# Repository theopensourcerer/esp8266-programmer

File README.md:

# esp8266-programmer
WIP - ESP Device Programmer without solder

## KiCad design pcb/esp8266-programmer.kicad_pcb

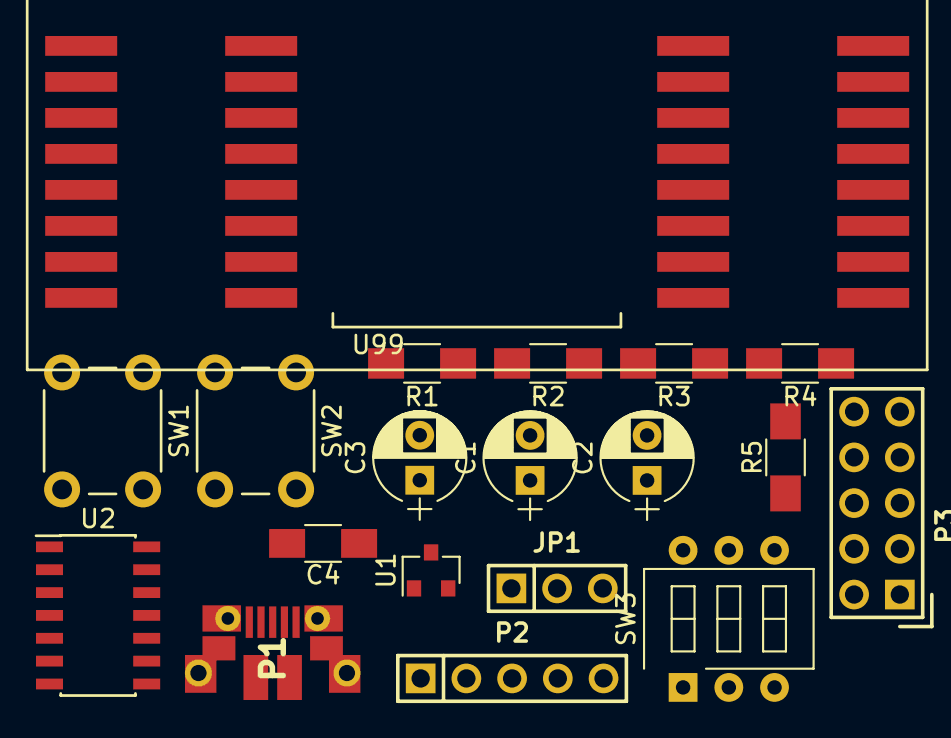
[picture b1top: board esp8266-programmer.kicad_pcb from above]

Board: 2 copper layers, 19 parts (0 on the bottom side), 23 nets, no tracks yet.

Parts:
C1: 1uF; CP_Radial_D5.0mm_P2.50mm
C2: 330uf; CP_Radial_D5.0mm_P2.50mm
C3: 4.7uF; CP_Radial_D5.0mm_P2.50mm
C4: 330nF; C_1206_HandSoldering
JP1: Jumper_NO_Dual; SIL-3
P1: USB_OTG; USB-MICROB-FCI-10103592
P2: CONN_01X04; SIL-5
P3: CONN_02X05; DIL-5
R1, R2, R3, R4, R5: 10K; R_1206_HandSoldering
SW1: RESET; SW_PUSH_6mm_h4.3mm
SW2: FLASH; SW_PUSH_6mm_h4.3mm
SW3: SW_DP3T; SW_DIP_x3_W7.62mm_Slide_LowProfile
U1: MCP1700T-3302E/TT; SOT-23
U2: MCP2221-I/SL; SOIC-14_3.9x8.7mm_Pitch1.27mm
U99: ESP-12; ESP-12-with-pogo-pin-pads

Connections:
/D+: P1.3, U2.13
/D-: P1.2, U2.12
/PP_ADC: P3.1, U99.2
/PP_CH_EN: R2.2, U99.3
/PP_GPIO0: P3.6, R3.2, SW2.2, U99.12
/PP_GPIO2: P3.8, R4.2, U99.11
/PP_GPIO4: P3.4, U99.13
/PP_GPIO5: P3.2, U99.14
/PP_GPIO12: P3.7, U99.6
/PP_GPIO13: P3.9, U99.7
/PP_GPIO14: P3.5, U99.5
/PP_GPIO15: P3.10, R5.1, U99.10
/PP_GPIO16: JP1.2, P3.3, U99.4
/PP_REST: JP1.1, R1.2, SW1.2, U99.1
/PP_RXD: U2.6, U99.15
/PP_TXD: U2.5, U99.16
GND: C1.2, C2.2, C3.2, C4.2, P1.5, P2.4, R5.2, SW1.1, SW2.1, U1.1, U2.14, U99.9
unnamed: C1.1, SW3.3, U1.3
unnamed: C4.1, U2.11
unnamed: P2.1, SW3.2
unnamed: P2.2, SW3.5
VBUS: P1.1, SW3.1
VCC: C2.1, C3.1, R1.1, R2.1, R3.1, R4.1, SW3.6, U2.1, U99.8

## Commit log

2017-03-28 Add pcb directory and vanilla KiCad project
2017-03-29 Edit PCB schematic with some random design thoughts
2017-04-01 Edit Kicad schematic to add basic components
2017-04-01 Edit Kicad schematic to add basic components (again)
2017-04-01 Add ESP chip, USB chip and some pin designations
2017-04-02 Add custom Kicad libs directory to project directory
2017-04-03 Add kicad_modules directory & create pogo pin footprint
2017-04-04 Create kicad_extras directory for libs, modules, 3d shapes. Move relevant files. Set relative paths for libs
2017-04-05 Fix wiring for switches. Add GPIO conns
2017-04-06 Add tri-state buffer parts
2017-04-08 Add tri-state buffers. Wire MCP2221
2017-04-13 Interim stage
2017-04-14 Interim stage - Part 2
2017-04-24 Add CH340G and new reset/flash circuit
2017-04-25 Add final components for CH230G & RST/FLA switch
